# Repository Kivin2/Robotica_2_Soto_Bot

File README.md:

# SOTO Bot con Nvidia Jetson Nano
Aqui veremos la experimentacion que tuvo lugar con la Nvidia Jetson Nano para desarrollar herramientas utiles a la hora de construir a SOTOBOT.

## 1. Que es una Jetson Nano

Nvidia Jetson nano es una plataforma de desarrollo creada por Nvidia para aplicaciones de inteligencia artificial y deep learning. Es una opcion atractiva ya que los microcontroladores que usualmente se utilizaban para los desarrollos de prototipos o experimentacion mas "casera" carecian de poder de procesamiento para utilizarlas en aplicaciones de inteligencia atificial.

##### Nvidia Jetson Nano Developer Kit: Rev B01

##### Especificaciones Tecnicas

| Sector | Especificacion |
| ------------- | ------------- |
| **GPU**  | 128-core Maxwell  |
| **CPU**  | Quad-core ARM A57 @ 1.43 GHz  |
| **Memory **  | 4 GB 64-bit LPDDR4 25.6 GB/s |
| **Storage**  | microSD (not included)  |
| **Camera**  | 2x MIPI CSI-2 DPHY lanes  |
| **Connectivity**  | Gigabit Ethernet, M.2 Key E  |
| **Display**  | HDMI and display port  |
| **USB**  | 4x USB 3.0, USB 2.0 Micro-B  |
| **Others**  | GPIO, I2C, I2S, SPI, UART |

### Primeros Pasos
Para comenzar a utilizar la Jeson Nano se necesita:
- Alimentacion
	- 5V y 2.5 o 4 A dependiendo del metodo de alimentacion (Adaptador micro-USB o adaptador jack de barril).
- MicroSD (se recomienda minimo 32GB USH-1, al principio se utilizo de este tamaño pero luego se lleno y dejo de bootear el OS por lo que es cambio a una de 64GB)
- Teclado y Raton USB
- Pantalla HDMI
- Internet a traves de cable Ethernet

De aqui se siguen los pasos de la  [Guia de Inicio](https://developer.nvidia.com/embedded/learn/get-started-jetson-nano-devkit) oficial de Nvidia.

En pocas palabras se descarga el OS, el cual es una version de Ubuntu. Se quema el OS en la tarjeta SD a traves de un adaptador y un software especifico, y finalmente se inserta la tarjeta con el OS en la placa. Se conectan todos los perifericos necesarios y luego se conecta la alimentacion. Apenas se conecte la alimentacion la Jetson Nano se prenderá y podras comenzar la configuracion inicial de la tarjeta.

## 2. Primeras Configuraciones
El sistema operativo es Linux. Por lo que necesitamos varios programas y paquetes antes de siquiera empezar a usar la tarjeta.

### Visual Studio Code
Para esto se puede descargar el paquete directamente de la pagina de Visual Studio Code y luego instalarlo por la linea de comandos.

La otra manera es clonar un repositorio de github que consitne un script que te instala VScode a su ultima version automaticamente. Yo lo hice de la ultima manera.

```
$ git clone https://github.com/JetsonHacksNano/installVSCode.git
$ cd installVSCode
$ ./installVSCodeWithPython.sh
```
Este scrip instala VSCode con la extension de Python ya integrada. Por lo que podemos empezar a programar en python inmediatamente. Las librerias que se iran utilizando se tienen que instalar de forma independiente (pip, numpy, matplotlib, pygame, etc.)

### Camara
La camara utilizada en este caso es la Raspbery pi Arducam imx519. Para que fucione se tiene que descargar los drivers. Esto se hace siguiento los pasos de la [guia de Arducam](https://docs.arducam.com/Nvidia-Jetson-Camera/Native-Camera/Quick-Start-Guide/).
Tambien se debe instalar v4l-utils, el cual es una serie de paquetes para manejar dispositivos multimedia. Esto se hace con el siguiente comando:
```
$ sudo apt-get install v4l-utils
```
Se descubrio a traves de diferentes testeos que una camara USB seria una mejor opcion ya que la raspberry pi cam se le hace funcionar a traves de un codificador llamado Gstreamer, lo que añade mas dificultad a cualquier programa que utilice video.

## 3. Desarrollo de Codigos
### OpenCV
OpenCV es una libreria de Python que permite trabajar con los frames que entrega una camara. A este frame se le puede aplicar diferentes filtros y metodos de calculo, lo que da inicio a la vision computacional. En el archivo *openCV1-Camera.py* se demuestra como obteniendo un frame y luego mostrandolo se puede visualizar el videostream.
En esta parte tambien se experimento con el dibujo encima de las imagenes, filtros, texto, etc.
### Reconocimiento Facial
Para esto primero se requiere instalar una libreria. Aunque primero se deben instalar algunos paquetes necesarios. Luego se tiene que clonar el repositorio donde esta la libreria de reconocimiento facial. Finalmente se tiene que reinciar para aplicar los cambios.
```
$ sudo apt-get install cmake libopenblas-dev liblapack-dev libjpg-dev
$ git clone https://github.com/JetsonHacksNano/installSwapfile
$ ./installSwapfile/installSwapfile.sh
$ sudo reboot now
```
ahora se tiene que instalar otro paquete y finalmente instalar la libreria:
```
$ wget http://dlib.net/files/dlib-19.17.tar.bz2
$ tar jxvf dlib-19.17.tar.bz2
$ ./installSwapfile/installSwapfile.sh
$ cd dlib-19.17.tar.bz2
$ sudo python3 setup.py install
$ sudo pip3 install face_recognition
```
Con todo esto ya se puede utilizar la libreria en los scripts de python. Estos Scripts estan en la carpeta *FaceRecognizer*

### Sensores
En un principio se pensaba usar distintos sensores conectados directamente a la Jetson Nano. Pero solo se pudo experimentar con el sensor MPU6050 el cual tiene una comunicacion I2C.

Existe una libreria para usar este sensor directamente con la jeston nano y se descarga de la siguiente manera:
```
$ sudo apt-get install adafruit-circuitpython-mpu6050
```
luego se puede probar a traves del script *MPU6050.py*

### Actuadores
Quien controla a los actuadores (motores brushless) es un arduino uno. Por lo que para esta parte solo se experimento con enviar cierta informacino de manera serial a un arduino conectado por USB a la Jetson Nano.

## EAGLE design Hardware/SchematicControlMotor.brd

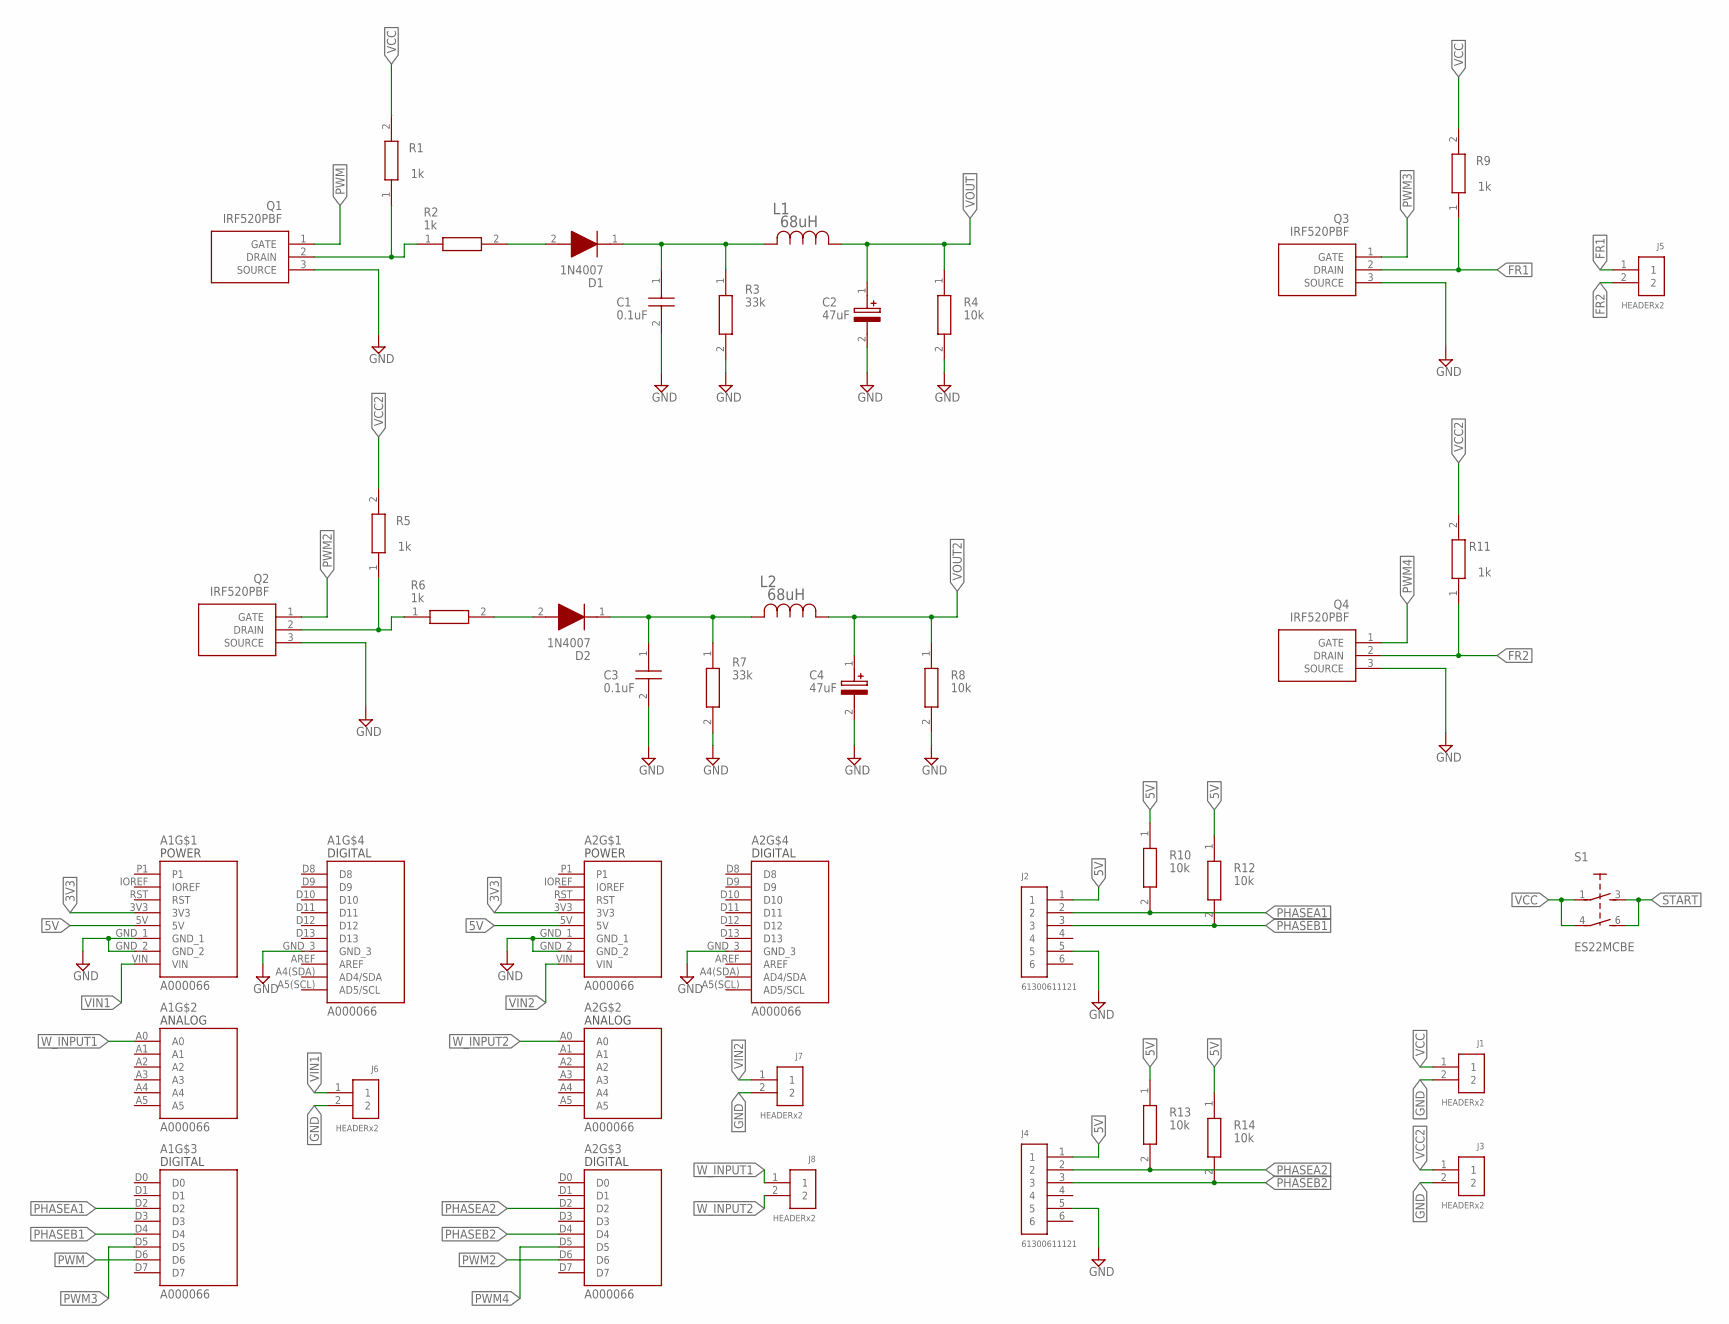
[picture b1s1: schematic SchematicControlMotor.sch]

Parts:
A1, A2: A000066; ARDUINO_A000066
C1, C3: 0.1uF; K104K10X7RF5TL2
C2, C4: 47uF; CAPPRD200W50D525H1100
D1, D2: 1N4007; DIOAD1405W58L465D235
J1, J3, J5, J6, J7, J8: HEADERx2; 61300211121
J2, J4: 61300611121
L1, L2: 68uH; IND_BOURNS_78F
Q1, Q2, Q3, Q4: IRF520PBF; TO254P465X1024X2050-3P
R1, R2, R5, R6, R9, R11: 1k; RESAD1041W46L381D165
R3, R7: 33k; RESAD1041W46L381D165
R4, R8, R10, R12, R13, R14: 10k; RESAD1041W46L381D165
S1: ES22MCBE

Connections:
3V3: A1.3V3, A2.3V3
5V: A1.5V, A2.5V, J2.1, J4.1, R10.1, R12.1, R13.1, R14.1
FR1: J5.1, Q3.2 (DRAIN), R9.1
FR2: J5.2, Q4.2 (DRAIN), R11.1
GND: A1.GND_1, A1.GND_2, A1.GND_3, A2.GND_1, A2.GND_2, A2.GND_3, C1.2, C2.2 (-), C3.2, C4.2 (-), J1.2, J2.5, J3.2, J4.5, J6.2, J7.2, Q1.3 (SOURCE), Q2.3 (SOURCE), Q3.3 (SOURCE), Q4.3 (SOURCE), R3.2, R4.2, R7.2, R8.2
unnamed: Q1.2 (DRAIN), R1.1, R2.1
unnamed: D1.2 (A), R2.2
unnamed: C1.1, D1.1 (K), L1.2, R3.1
unnamed: D2.2 (A), R6.2
unnamed: C3.1, D2.1 (K), L2.2, R7.1
unnamed: Q2.2 (DRAIN), R5.1, R6.1
PHASEA1: A1.D2, J2.2, R10.2
PHASEA2: A2.D2, J4.2, R13.2
PHASEB1: A1.D4, J2.3, R12.2
PHASEB2: A2.D4, J4.3, R14.2
PWM: A1.D6, Q1.1 (GATE)
PWM2: A2.D6, Q2.1 (GATE)
PWM3: A1.D5, Q3.1 (GATE)
PWM4: A2.D5, Q4.1 (GATE)
START: S1.3, S1.6
VCC: J1.1, R1.2, R9.2, S1.1, S1.4
VCC2: J3.1, R5.2, R11.2
VIN1: A1.VIN, J6.1
VIN2: A2.VIN, J7.1
VOUT: C2.1 (+), L1.1, R4.1
VOUT2: C4.1 (+), L2.1, R8.1
W_INPUT1: A1.A0, J8.1
W_INPUT2: A2.A0, J8.2

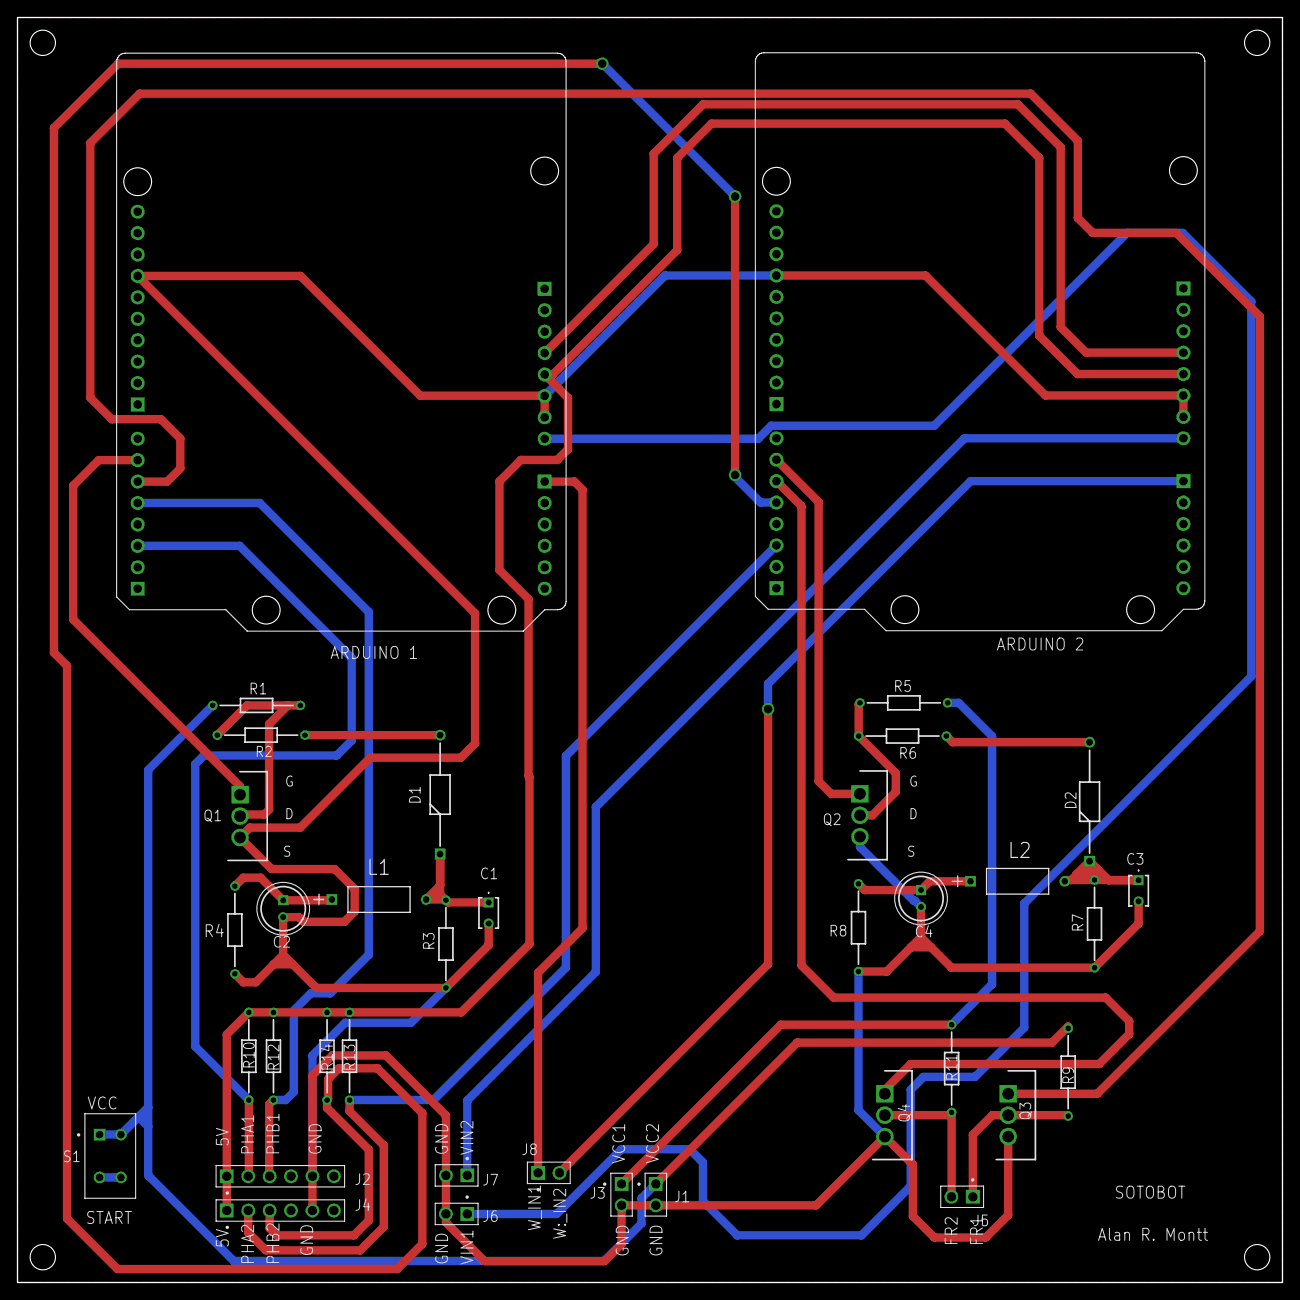
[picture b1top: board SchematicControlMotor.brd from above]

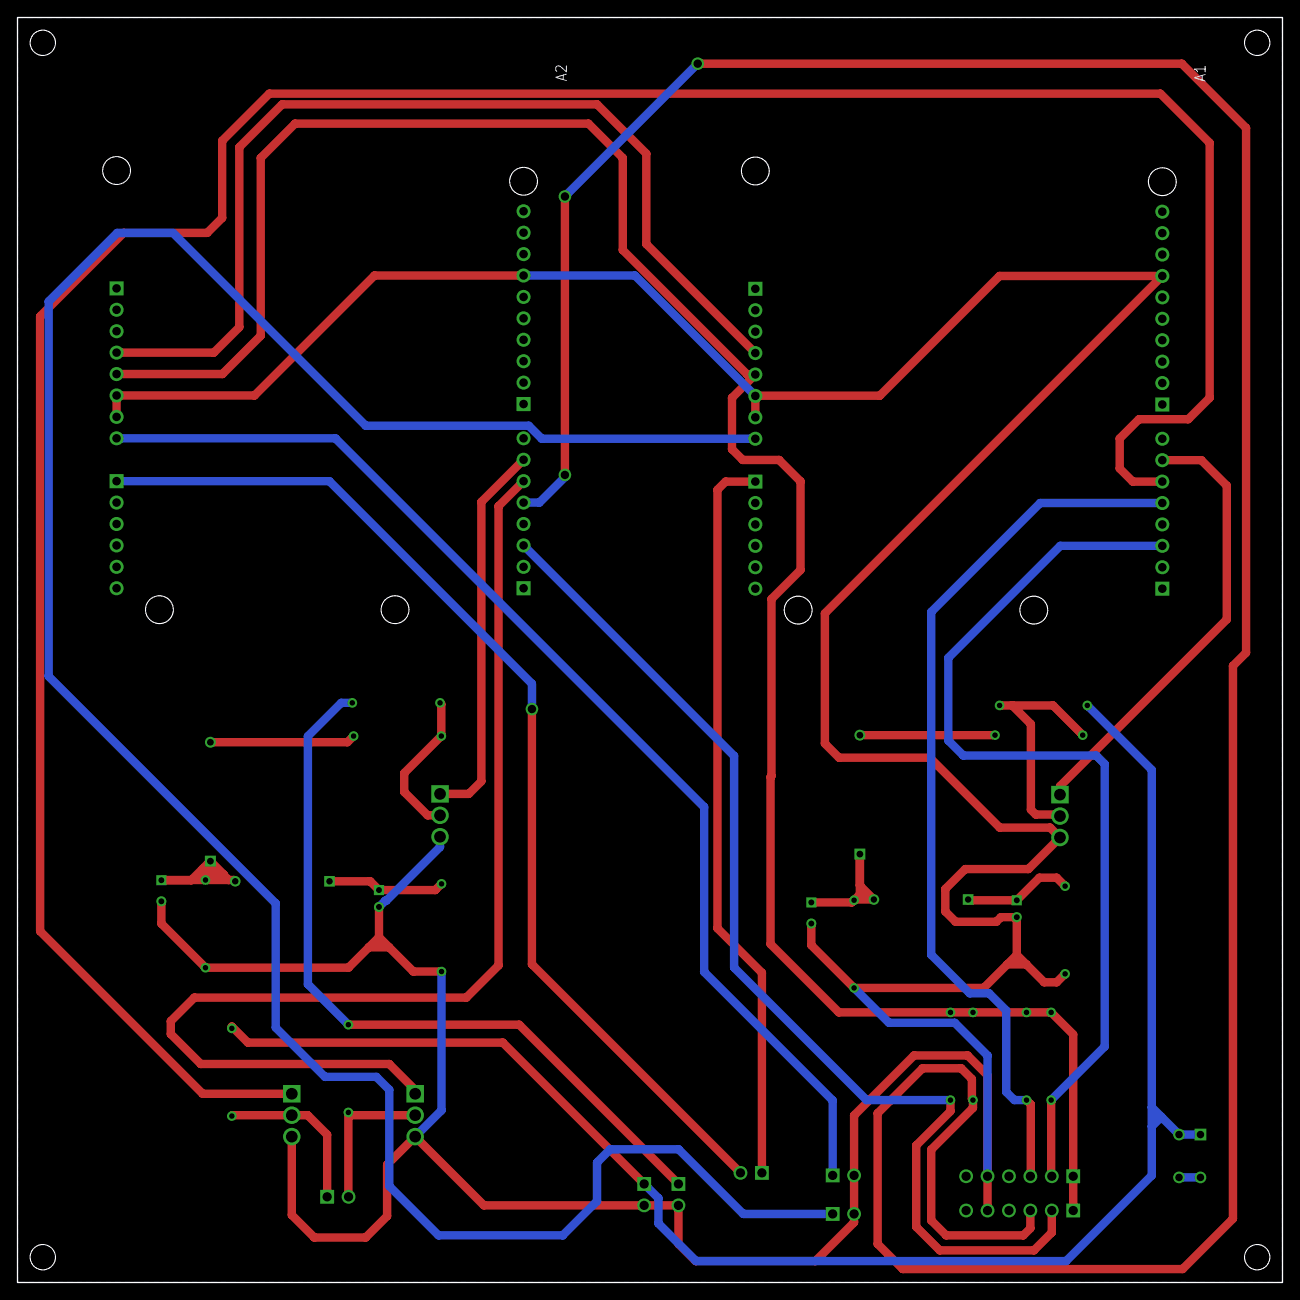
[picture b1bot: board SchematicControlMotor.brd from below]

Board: 2 copper layers, 150.0 x 150.0 mm, 37 parts (2 on the bottom side), 28 nets.

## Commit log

2023-05-17 Create Lidar
2023-05-18 Update Lidar
2023-05-18 Create GPS
2023-05-25 Update and rename Lidar to Tareas
2023-05-25 Update and rename Lidar to GPS
2023-05-25 Update and rename Lidar to IMU
2023-05-25 Update and rename Lidar to Documentos
2023-05-26 Actualizacion Tarea de Alan
    Solo añadi lo que Alan debe hacer
2023-05-26 Platformio Added
2023-05-26 Added the .cpp file for Arduino
2023-05-26 More files added
2023-05-26 Added Footprint Arduino for PCB
2023-05-27 Updated 3D Model for Arduino Footprint
2023-05-27 Update Tareas
2023-05-27 README Added
2023-05-27 README Updated
2023-05-31 Circuit Updated
2023-05-31 List of Components Updated
2023-06-08 Rename Lidar to Lidar.ino
2023-06-10 Tareas
2023-06-10 PCB Design added
2023-06-13 Rename IMU.py to imu.py
2023-06-13 Se añadio un README
2023-06-21 avance de lectura con 2 mpus
2023-06-21 Create RPY_2MPUS
2023-06-21 librerias usadas
2023-06-27 Orientación tridimensional de la IMU-MPU6050
    El esquema de código trabaja con la obtención de datos del acelerómetro en conjunto con el giroscopio del MPU6050, usando solo la biblioteca wire.h para la comunicación I2C de la IMU.
    Los cálculos de giro de cada ángulo (pitch, yaw and roll) están basados en la teoría de quaternios y el algoritmo de filtrado Mahony AHRS.
2023-06-27 Create ServoMotor
2023-06-27 Updated code
2023-06-28 Update ServoMotor
2023-07-19 Create Leame.Diseño
    diseño mecanico_base
2023-07-19 Add files via upload
    aqui se encuentra la base mecanica del prototipo del robot.
2023-07-19 Rename Leame.Diseño to Leame.Diseño.md
2023-07-21 Create Mapeo y Astar
2023-07-21 New PCB and Code
2023-07-21 Create Matlab codes
2023-07-21 Update Matlab codes
2023-07-21 New README
2023-07-21 Update codigo main algoritmo Astar
2023-07-21 Update Astar main code
2023-07-21 Primer avance
2023-07-21 calibracion del mpu
2023-07-21 libreria para comunicacion I2C raspberry
2023-07-21 libreria para imu.py
2023-07-21 libreria para angulos euler R-P-Y
2023-07-21 R-P-Y
2023-07-21 frist commit
2023-07-21 openCV1
2023-07-21 Create img
2023-07-21 Create imu
2023-07-21 Create im
2023-07-21 Rename RPY_2MPUS to RPY_2MPUS.py
2023-07-21 Add files via upload
    El A* es un algoritmo de búsqueda en grafos utilizado para encontrar el camino o ruta mas cortos (optimo) entre 2 puntos.
    El Algoritmo utiliza algunas funciones como:
    Heurística que estima los costos para llegar a la meta a través de los nodos.
    Costos que combina el costo real para llegar a un nodo y la anterior nombrada heurística
    Nuestra problemática era atravesar la universidad desde un extremo a otro considerando cada camino utilizable en la universidad.
    Junto a esto se decidió manualmente bloquear caminos,
2023-07-21 Create Astar Funcionamiento
2023-07-21 Documentación Orientación con MPU6050
    Descripción del trabajo realizado para obtener el R-P-Y y de esta manera saber la orientación del sensor MPU6050 para futura aplicación en el proyecto del robot diferencial de 2 ruedas

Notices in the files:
parts and their libraries:
COPYRIGHT: Copyright (C) 2023 Ultra Librarian. All rights reserved.
